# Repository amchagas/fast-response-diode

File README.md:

# fast-response-diode
a circuit to measure fast changing light signals down to hundreds of microseconds

#### Previous work:
This board is based on this article <https://www.mikrocontroller.net/articles/Lichtsensor_/_Helligkeitssensor>

- fast_diode_pcb folder has the PCB files to produce this board as well as the bill of materials.

This board and components can be ordered easily at [kitspace](https://kitspace.org/boards/github.com/amchagas/fast-response-diode/)

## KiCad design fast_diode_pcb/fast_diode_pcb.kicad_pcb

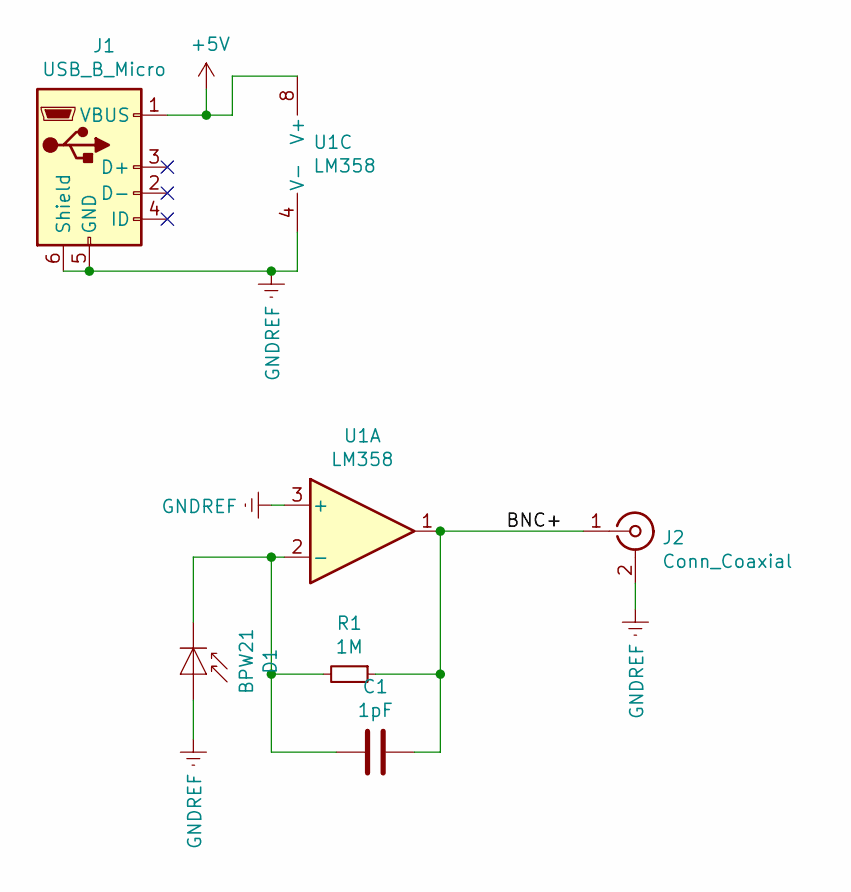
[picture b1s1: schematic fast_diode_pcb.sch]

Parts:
C1: 1pF; C_Disc_D4.3mm_W1.9mm_P5.00mm
D1: BPW21; TO-5-2_Window
J1: USB_B_Micro; USB_Micro-B_Molex_47346-0001
J2: Conn_Coaxial; BNC_Amphenol_B6252HB-NPP3G-50_Horizontal
R1: 1M; R_Axial_DIN0207_L6.3mm_D2.5mm_P10.16mm_Horizontal
U1: LM358; SOIC-8_5.23x5.23mm_P1.27mm

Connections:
+5V: J1.1 (VBUS), U1.8 (V+)
/BNC+: C1.1, J2.1 (In), R1.1, U1.1
GNDREF: D1.1 (A), J1.5 (GND), J1.6 (Shield), J2.2 (Ext), U1.3 (+), U1.4 (V-)
unnamed: C1.2, D1.2 (K), R1.2, U1.2 (-)

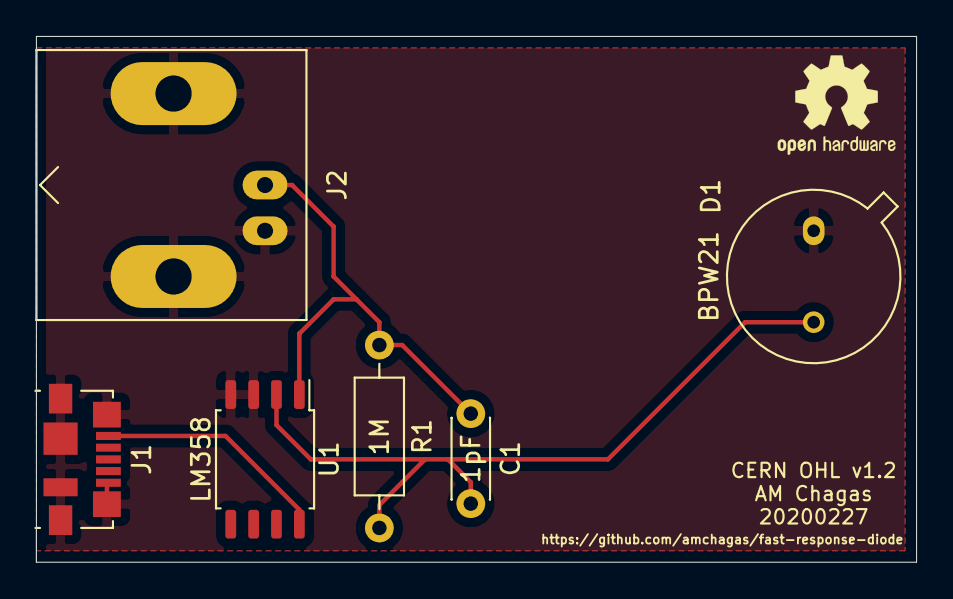
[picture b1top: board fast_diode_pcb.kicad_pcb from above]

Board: 2 copper layers, 48.9 x 29.2 mm, 6 parts (0 on the bottom side), 4 nets.

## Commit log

2020-02-26 documentation plus board
2020-02-27 first pcb design
2020-02-27 update pcb
2020-03-18 board updates
2020-03-26 update pcb and prepare for kitspace
2020-03-26 add gerbers to kitspace.yaml
2022-06-01 Add kitspace.org link
2024-01-16 make paths for carving a board with carvera

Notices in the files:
fast_diode_pcb/fast_diode_pcb.kicad_pcb:
CERN OHL v1.2
